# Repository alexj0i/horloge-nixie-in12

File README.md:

# Horloge nixie IN-12

Afficheur 4 chiffres à tubes nixie **IN-12A / IN-12B**, avec deux points en néons **INS-1**.
Un décodeur **SN74141 / K155ID1** par tube (pilotage statique). Chaque tube est monté sur son propre porte-tube, enfiché sur la carte mère.
Deux cartes empilées derrière la carte mère remplacent l'Arduino Uno et le module HT (tout en traversant) : une carte logique (ATmega328P, 74HC595, horloge DS1307) et une carte alimentation (12 V, 5 V, 170 V intégré, boutons).

## Contenu

| Dossier | Contenu | État |
|---|---|---|
| `porte_tube_in12/` | Porte-tube individuel 25,4 × 36 mm, tube sur 12 douilles Ø 1 mm, R d'anode 12 kΩ | v1.0 terminé |
| `porte_tube_in12/fabrication/` | Gerbers + perçages prêts pour JLCPCB | à jour avec v1.0 |
| `carte_mere_in12/` | Carte mère 114,3 × 36 mm : 4 supports de porte-tubes, 4 × SN74141, 2 néons INS-1, connecteurs | schéma v0.3, routage en cours |
| `carte_mere_in12/docs/` | Schéma de la carte mère en PDF | v0.3 |
| `carte_logique_in12/` | Carte logique 114,3 × 36 mm, contre la carte mère : ATmega328P, 2 × 74HC595, DS1307, pilotage des deux points | schéma v0.1, composants placés, à router |
| `carte_alim_in12/` | Carte alimentation 114,3 × 36 mm, à l'arrière : jack 12 V, 5 V (L7805), 170 V (MC34063A + IRF740), coupure HT, boutons, ICSP, FTDI, pile CR1220 | schéma v0.1, composants placés, à router |
| `carte_*_in12/docs/` | Schémas en PDF et vues de placement | v0.1 |
| `firmware/nixie_in12/` | Programme Arduino pour le montage avec un Uno (horloge, affichage d'un nombre, anti-empoisonnement) | fonctionnel, à réécrire pour les nouvelles cartes |
| `docs/` | Photos du tube IN-12 et du néon INS-1 | |

Projets KiCad 10. Les symboles et empreintes sont dans chaque dossier de projet (`*.kicad_sym`, `*.pretty`) : rien à installer.

## Carte mère : connecteurs

| Réf. | Rôle | Broches |
|---|---|---|
| J1–J8 | Supports des porte-tubes (gauche / droite de V1…V4) | gauche : K5 K4 K3 K2 K1 virgule – ; droite : K6 K7 K8 K9 K0 (clé) **+HT** |
| J9 | Commande V1, V2 (2×4, au dos) | 1-4 : V1 A B C D · 5-8 : V2 A B C D |
| J12 | Commande V3, V4 (2×4, au dos) | 1-4 : V3 A B C D · 5-8 : V4 A B C D |
| J10 | Logique (au dos) | 1 : +5 V · 2 : GND |
| J11 | Haute tension (au dos) | 1 : **+HT 170 V** · 2 : clé · 3 : GND |
| J13 | Deux points (au dos) | 1 : DOT1_A · 3 : DOT2_A · 5 : DOT_K (2 et 4 sans broche) |
| DS1, DS2 | Néons INS-1 dans l'espace central entre V2 et V3 | 1 : anode · 2 : cathode |

Empilement (entretoises M2 × 11 entre chaque carte, mêmes 16 trous) :
carte mère → **carte logique** (supports P1 à P5 sur J9, J12, J10, J11, J13) → **carte alimentation** (JB1 2 × 10 sur JA1, JB2 1 × 3 +HT sur JA2).

Liaison JA1/JB1 : 1 +5V · 2 GND · 3 RESET · 4 DTR · 5 MOSI · 6 MISO · 7 SCK · 8 RXD · 9 TXD · 10 HV_EN · 11 BTN_MODE · 12 BTN_PLUS · 13 BTN_MINUS · 14 LDR · 15 +5V · 16 GND · 17 +5V · 18 GND · 19 VBAT · 20 GND.
Liaison JA2/JB2 : 1 +HT · 2 sans broche · 3 GND.

Câblage vers l'Uno attendu par le programme (`BCD_PIN`) :

| Tube | A | B | C | D |
|---|---|---|---|---|
| V1 (J9 1-4) | D13 | D11 | D10 | D12 |
| V2 (J9 5-8) | D9 | D7 | D6 | D8 |
| V3 (J12 1-4) | D5 | D3 | D2 | D4 |
| V4 (J12 5-8) | A3 | A1 | A0 | A2 |

Masse commune entre l'Arduino, la carte mère et le module HT.

## Programme

Moniteur série 9600 bauds, fin de ligne « Nouvelle ligne » :
`T1435` règle l'heure à 14:35 · `N42` affiche 42 · `H` retour à l'horloge · `C` défilement anti-empoisonnement.

## Reste à faire

- Carte mère : relier le +5 V entre V1, V2 et V3, et la masse de C1 ; placer et router DS1, DS2, J13 ; DRC à 0 avant commande.
- Cartes logique et alimentation : router les PCB (composants déjà placés), puis réécrire le firmware (74HC595, DS1307, boutons, coupure HT, deux points).
- Mesurer le diamètre de la queue des douilles (perçage prévu pour 0,5–0,75 mm).
- Vérifier le brochage sur un vrai tube avant de souder (anode = broche 1).
- Option : points de séparation INS-1 dans l'espace central de la carte mère.

## Sécurité

170 V continu sur les porte-tubes et J11. Débrancher l'alimentation et attendre que la sortie HT soit sous 10 V avant de toucher la carte.

## Travailler sur deux PC

Un seul PC à la fois sur un même projet : **Fetch/Pull** avant d'ouvrir KiCad, **Commit + Push** après l'avoir fermé.

## Licence

[CC BY-NC-SA 4.0](LICENSE) : fabrication et modifications libres pour un usage personnel, en citant l'auteur. **Vente et usage commercial interdits** sans accord écrit. Les versions modifiées doivent être publiées sous la même licence.
Quelques empreintes et symboles viennent des bibliothèques KiCad et restent sous CC-BY-SA 4.0 : voir [LICENCES.md](LICENCES.md).

Projet fourni sans garantie. Il utilise une haute tension de 170 V : si vous le reproduisez, c'est à vos risques.

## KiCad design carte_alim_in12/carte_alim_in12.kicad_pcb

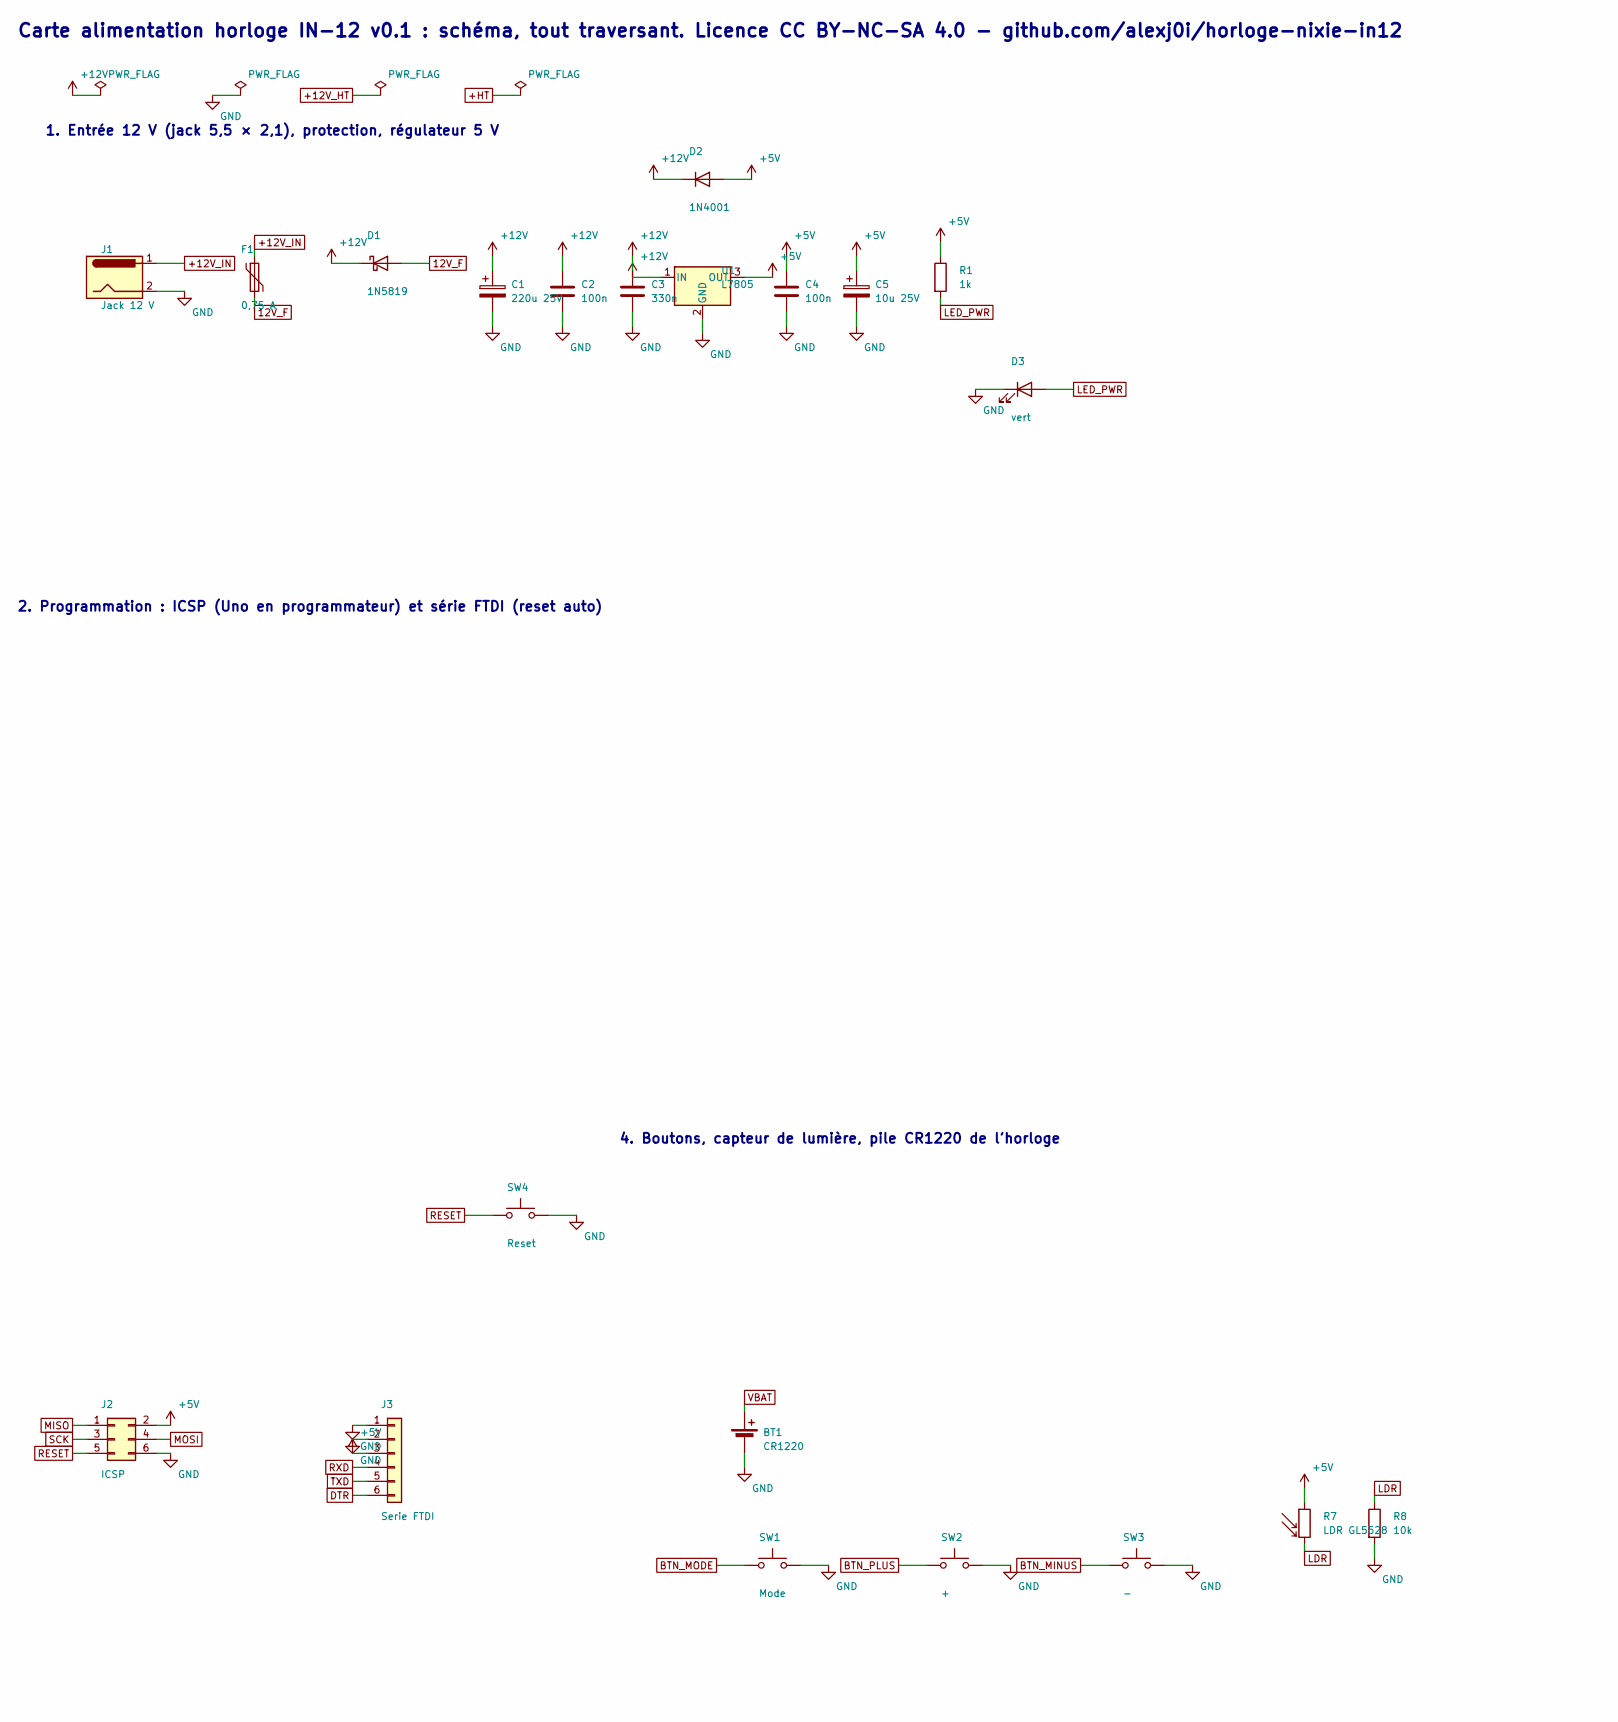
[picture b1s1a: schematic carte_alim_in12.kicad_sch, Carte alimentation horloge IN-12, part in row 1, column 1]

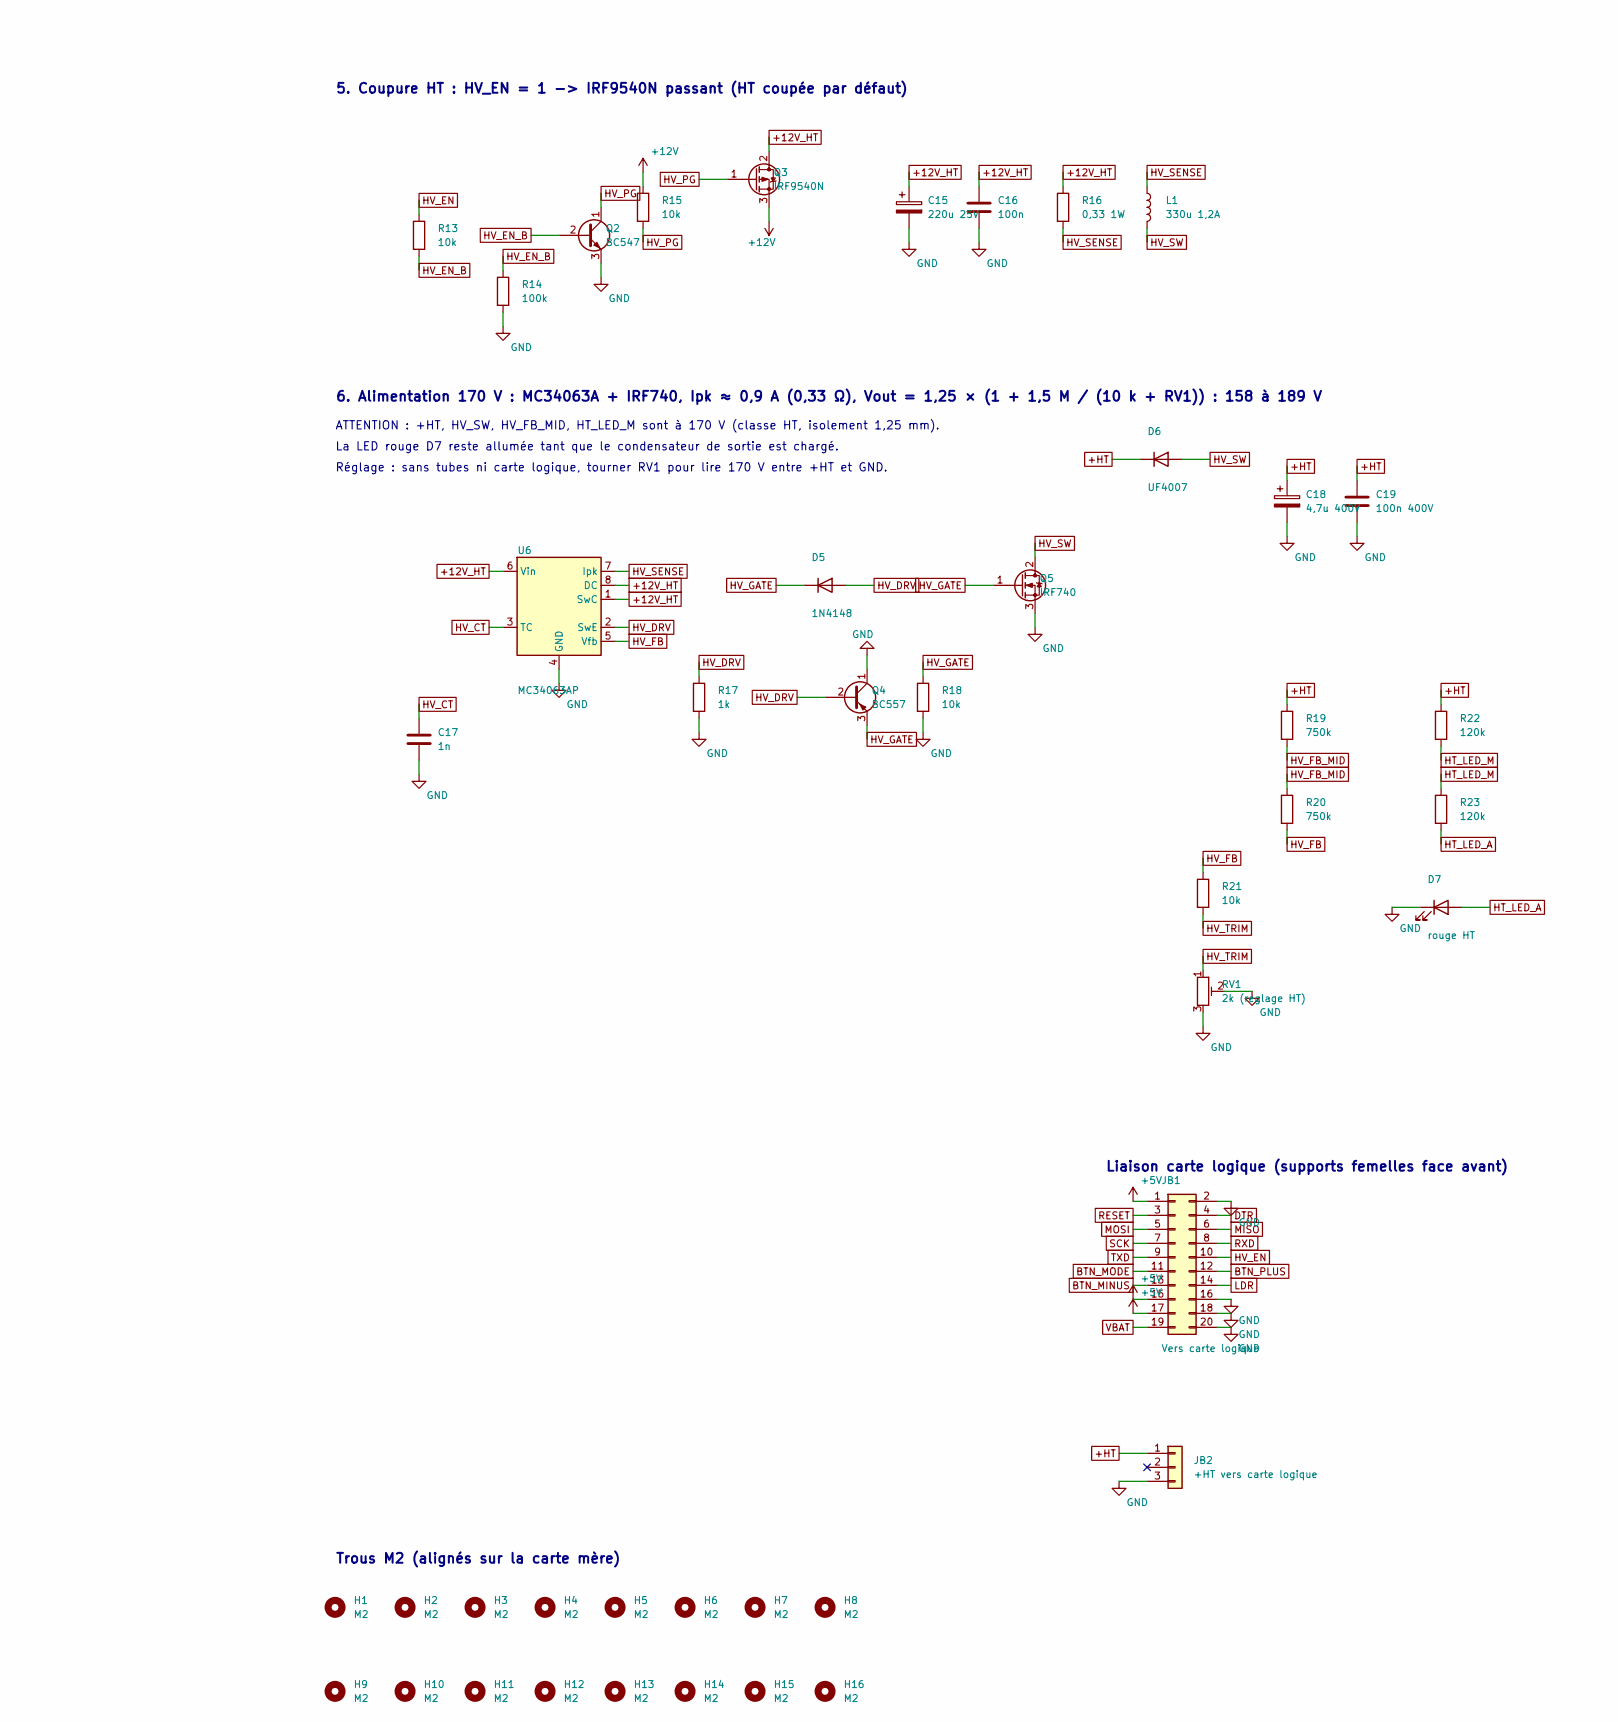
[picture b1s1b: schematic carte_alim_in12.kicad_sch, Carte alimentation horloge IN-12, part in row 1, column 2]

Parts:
BT1: CR1220; BatteryHolder_Keystone_3001_1x12mm
C1, C15: 220u 25V; CP_Radial_D8.0mm_P3.50mm
C2, C4, C16: 100n; C_Disc_D3.0mm_W1.6mm_P2.50mm
C3: 330n; C_Disc_D3.0mm_W1.6mm_P2.50mm
C5: 10u 25V; CP_Radial_D5.0mm_P2.00mm
C17: 1n; C_Disc_D3.0mm_W1.6mm_P2.50mm
C18: 4,7u 400V; CP_Radial_D10.0mm_P5.00mm
C19: 100n 400V; C_Rect_L10.0mm_W4.0mm_P7.50mm_FKS3_FKP3
D1: 1N5819; D_DO-41_SOD81_P3.81mm_Vertical_AnodeUp
D2: 1N4001; D_DO-41_SOD81_P3.81mm_Vertical_AnodeUp
D3: vert; LED_D3.0mm
D5: 1N4148; D_DO-35_SOD27_P7.62mm_Horizontal
D6: UF4007; D_DO-41_SOD81_P10.16mm_Horizontal
D7: rouge HT; LED_D3.0mm
F1: 0,75 A; Fuse_BelFuse_0ZRE0075FF_L11.5mm_W4.8mm
H1, H2, H3, H4, H5, H6, H7, H8, H9, H10, H11, H12, H13, H14, H15, H16: M2; MountingHole_2.2mm_M2
J1: Jack 12 V; BarrelJack_Horizontal
J2: ICSP; PinHeader_2x03_P2.54mm_Vertical
J3: Serie FTDI; PinHeader_1x06_P2.54mm_Vertical
JB1: Vers carte logique; PinSocket_2x10_P2.54mm_Vertical
JB2: +HT vers carte logique; Socket_1x03_Cle2
L1: 330u 1,2A; L_Radial_D12.5mm_P7.00mm_Fastron_09HCP
Q2: BC547; TO-92_Inline
Q3: IRF9540N; TO-220-3_Vertical
Q4: BC557; TO-92_Inline
Q5: IRF740; TO-220-3_Vertical
R1, R17: 1k; R_Axial_DIN0207_L6.3mm_D2.5mm_P2.54mm_Vertical
R7: LDR GL5528; R_LDR_5.1x4.3mm_P3.4mm_Vertical
R8, R13, R15, R18, R21: 10k; R_Axial_DIN0207_L6.3mm_D2.5mm_P2.54mm_Vertical
R14: 100k; R_Axial_DIN0207_L6.3mm_D2.5mm_P2.54mm_Vertical
R16: 0,33 1W; R_Axial_DIN0414_L11.9mm_D4.5mm_P5.08mm_Vertical
R19, R20: 750k; R_Axial_DIN0207_L6.3mm_D2.5mm_P7.62mm_Horizontal
R22, R23: 120k; R_Axial_DIN0207_L6.3mm_D2.5mm_P7.62mm_Horizontal
RV1: 2k (reglage HT); Potentiometer_Bourns_3296W_Vertical
SW1: Mode; SW_PUSH_1P1T_6x3.5mm_H5.0_APEM_MJTP1250
SW2: +; SW_PUSH_1P1T_6x3.5mm_H5.0_APEM_MJTP1250
SW3: -; SW_PUSH_1P1T_6x3.5mm_H5.0_APEM_MJTP1250
SW4: Reset; SW_PUSH_1P1T_6x3.5mm_H5.0_APEM_MJTP1250
U1: L7805; TO-220-3_Vertical
U6: MC34063AP; DIP-8_W7.62mm

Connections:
12V_F: D1.2 (A), F1.2
+5V: C4.1, C5.1, D2.2 (A), J2.2, J3.3, JB1.1, JB1.15, JB1.17, R1.1, R7.1, U1.3 (OUT)
+12V: C1.1, C2.1, C3.1, D1.1 (K), D2.1 (K), Q3.3 (S), R15.1, U1.1 (IN)
+12V_HT: C15.1, C16.1, Q3.2 (D), R16.1, U6.1 (SwC), U6.6 (Vin), U6.8 (DC)
+12V_IN: F1.1, J1.1
+HT: C18.1, C19.1, D6.1 (K), JB2.1, R19.1, R22.1
BTN_MINUS: JB1.13, SW3.1
BTN_MODE: JB1.11, SW1.1
BTN_PLUS: JB1.12, SW2.1
DTR: J3.6, JB1.4
GND: BT1.2 (-), C1.2, C2.2, C3.2, C4.2, C5.2, C15.2, C16.2, C17.2, C18.2, C19.2, D3.1 (K), D7.1 (K), J1.2, J2.6, J3.1, J3.2, JB1.2, JB1.16, JB1.18, JB1.20, JB2.3, Q2.3 (E), Q4.1 (C), Q5.3 (S), R8.2, R14.2, R17.2, R18.2, RV1.2, RV1.3, SW1.2, SW2.2, SW3.2, SW4.2, U1.2 (GND), U6.4 (GND)
HT_LED_A: D7.2 (A), R23.2
HT_LED_M: R22.2, R23.1
HV_CT: C17.1, U6.3 (TC)
HV_DRV: D5.2 (A), Q4.2 (B), R17.1, U6.2 (SwE)
HV_EN: JB1.10, R13.1
HV_EN_B: Q2.2 (B), R13.2, R14.1
HV_FB: R20.2, R21.1, U6.5 (Vfb)
HV_FB_MID: R19.2, R20.1
HV_GATE: D5.1 (K), Q4.3 (E), Q5.1 (G), R18.1
HV_PG: Q2.1 (C), Q3.1 (G), R15.2
HV_SENSE: L1.1, R16.2, U6.7 (Ipk)
HV_SW: D6.2 (A), L1.2, Q5.2 (D)
HV_TRIM: R21.2, RV1.1
LDR: JB1.14, R7.2, R8.1
LED_PWR: D3.2 (A), R1.2
MISO: J2.1, JB1.6
MOSI: J2.4, JB1.5
RESET: J2.5, JB1.3, SW4.1
RXD: J3.4, JB1.8
SCK: J2.3, JB1.7
TXD: J3.5, JB1.9
VBAT: BT1.1 (+), JB1.19

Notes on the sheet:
1. Entrée 12 V (jack 5,5 × 2,1), protection, régulateur 5 V
2. Programmation : ICSP (Uno en programmateur) et série FTDI (reset auto)
4. Boutons, capteur de lumière, pile CR1220 de l'horloge
5. Coupure HT : HV_EN = 1 -> IRF9540N passant (HT coupée par défaut)
6. Alimentation 170 V : MC34063A + IRF740, Ipk ≈ 0,9 A (0,33 Ω), Vout = 1,25 × (1 + 1,5 M / (10 k + RV1)) : 158 à 189 V
Liaison carte logique (supports femelles face avant)
Trous M2 (alignés sur la carte mère)
ATTENTION : +HT, HV_SW, HV_FB_MID, HT_LED_M sont à 170 V (classe HT, isolement 1,25 mm).
La LED rouge D7 reste allumée tant que le condensateur de sortie est chargé.
Réglage : sans tubes ni carte logique, tourner RV1 pour lire 170 V entre +HT et GND.
Carte alimentation horloge IN-12 v0.1 : schéma, tout traversant. Licence CC BY-NC-SA 4.0 - github.com/alexj0i/horloge-nixie-in12

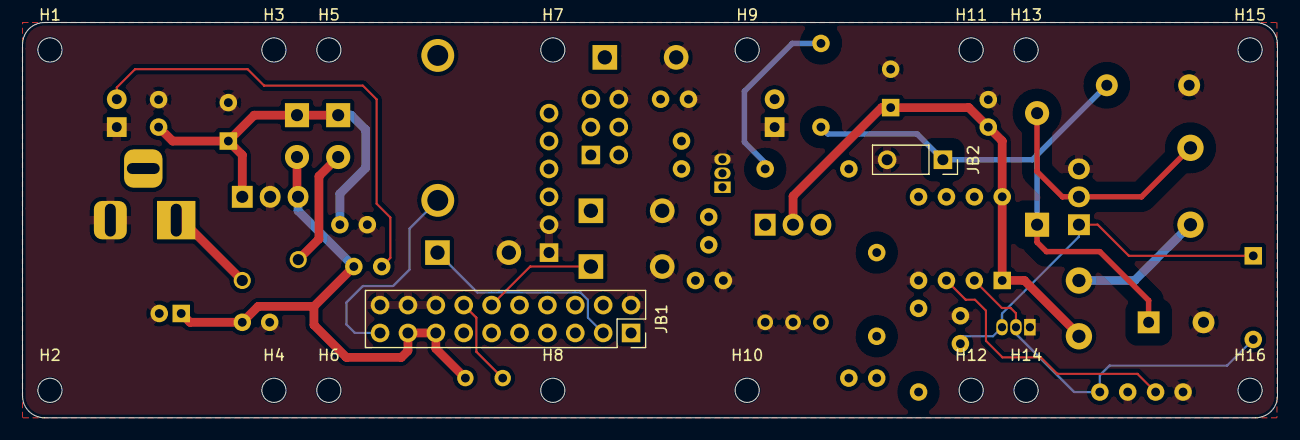
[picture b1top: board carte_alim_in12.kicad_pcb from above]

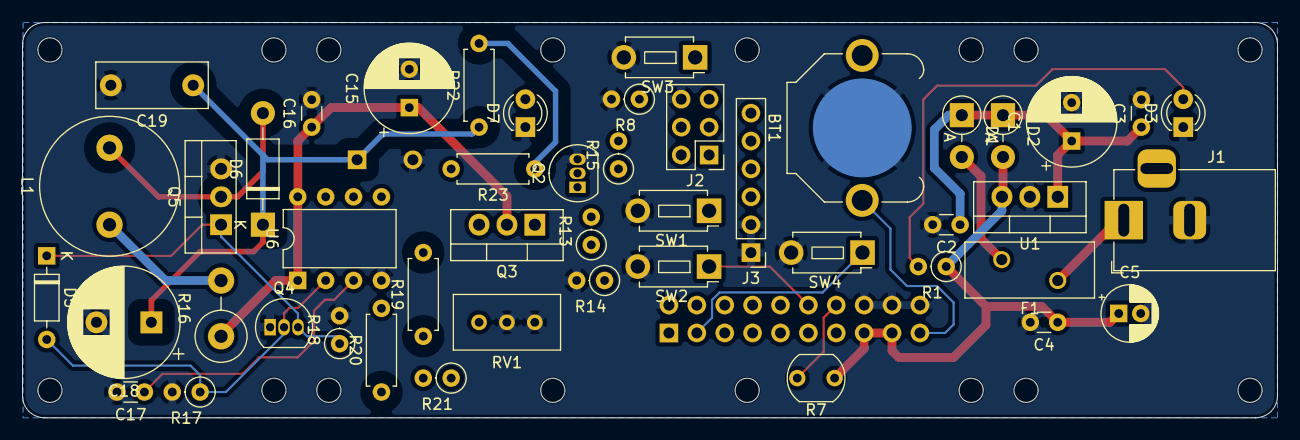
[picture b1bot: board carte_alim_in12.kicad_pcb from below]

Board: 2 copper layers, 114.3 x 36.0 mm, 65 parts (47 on the bottom side), 33 nets.

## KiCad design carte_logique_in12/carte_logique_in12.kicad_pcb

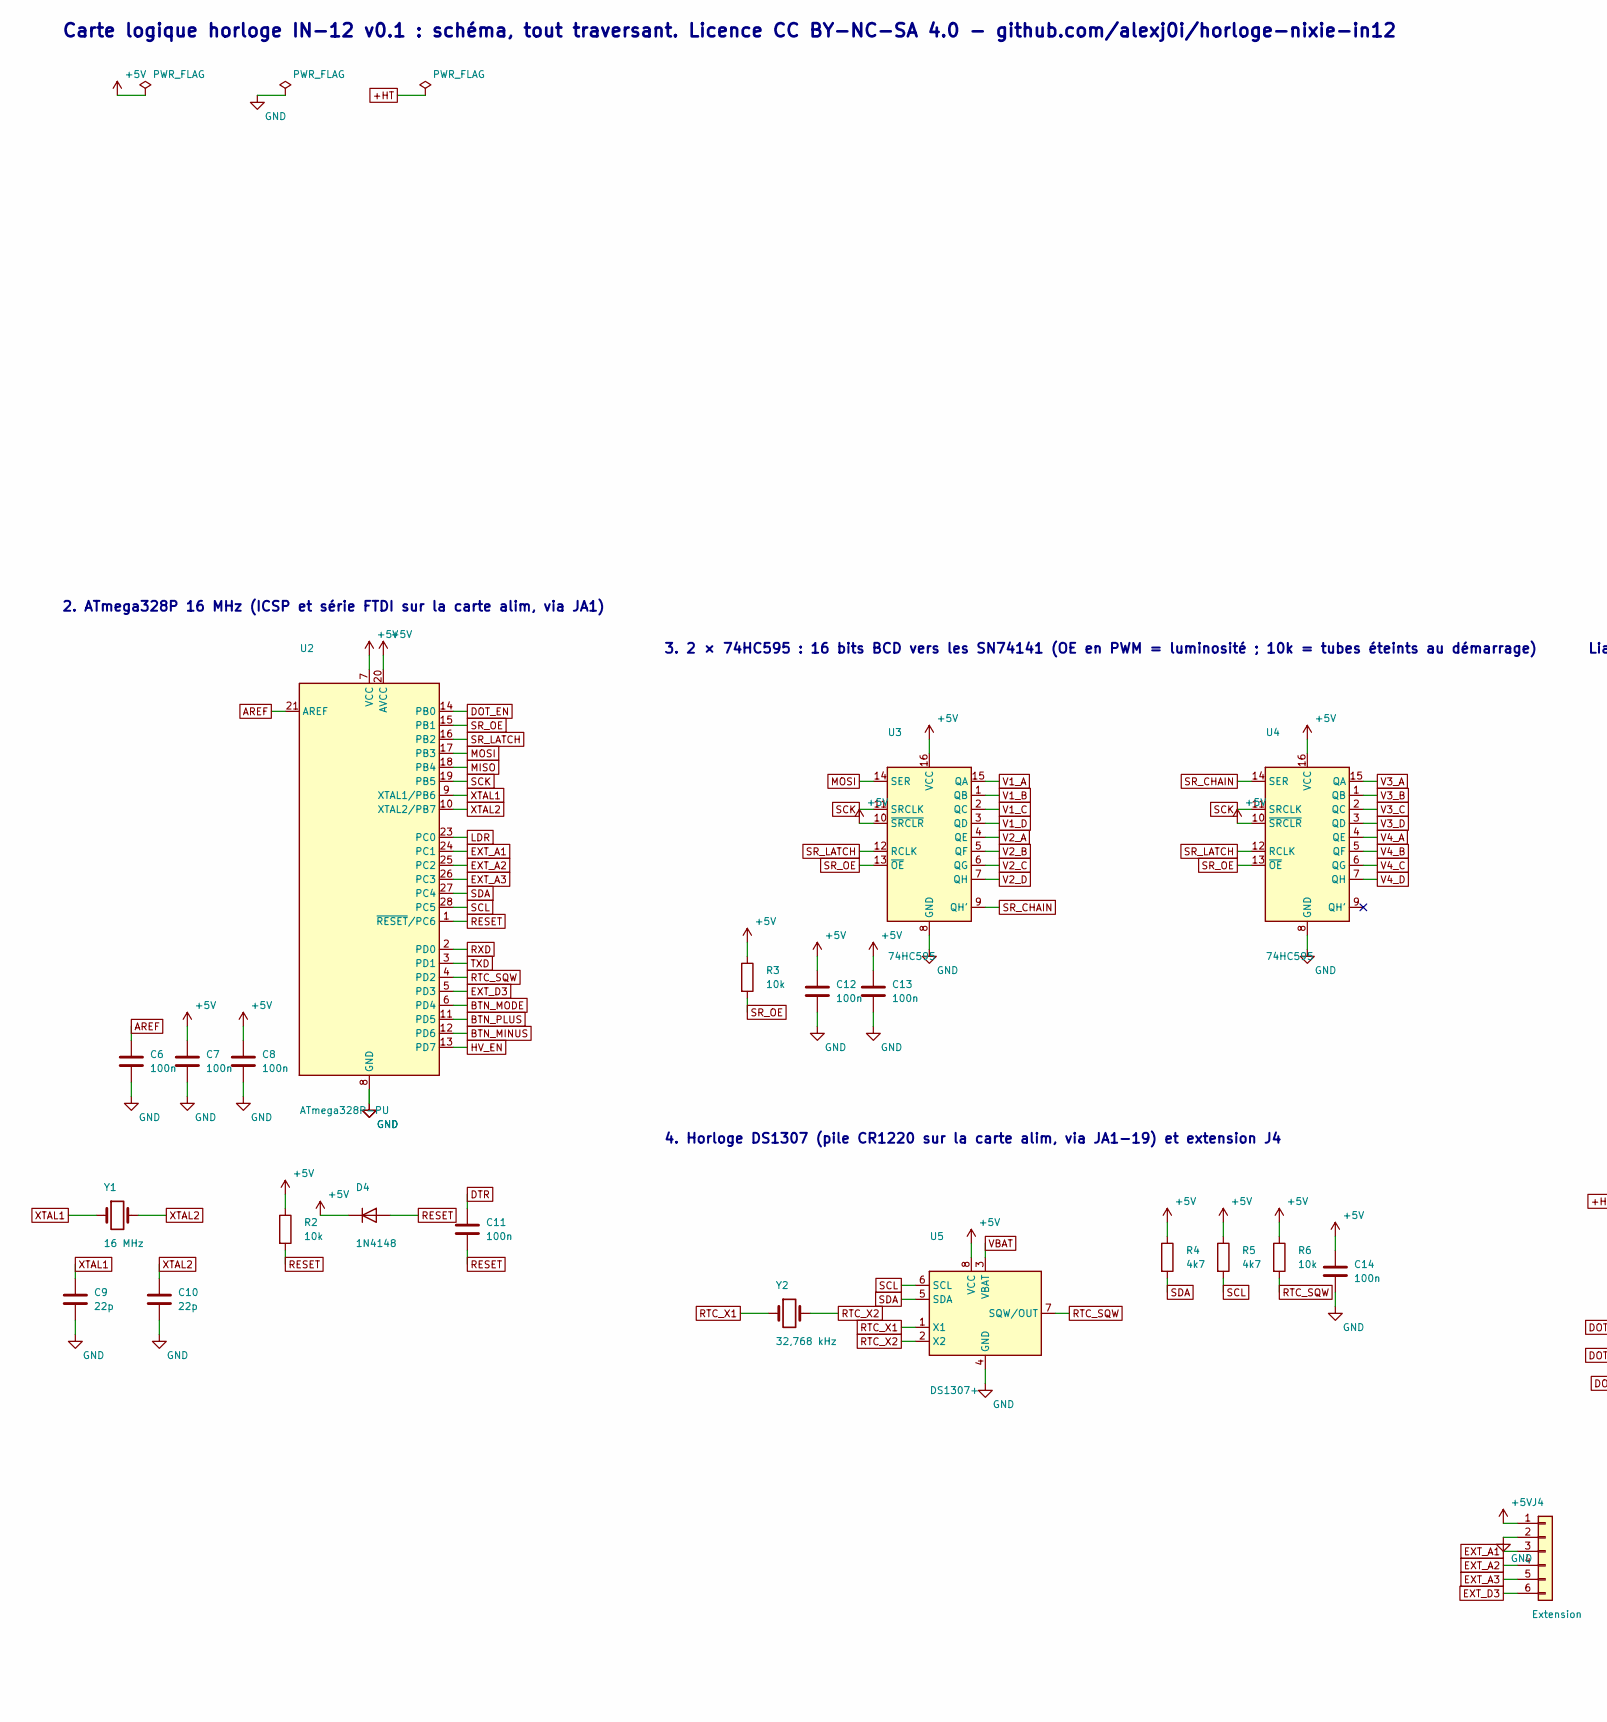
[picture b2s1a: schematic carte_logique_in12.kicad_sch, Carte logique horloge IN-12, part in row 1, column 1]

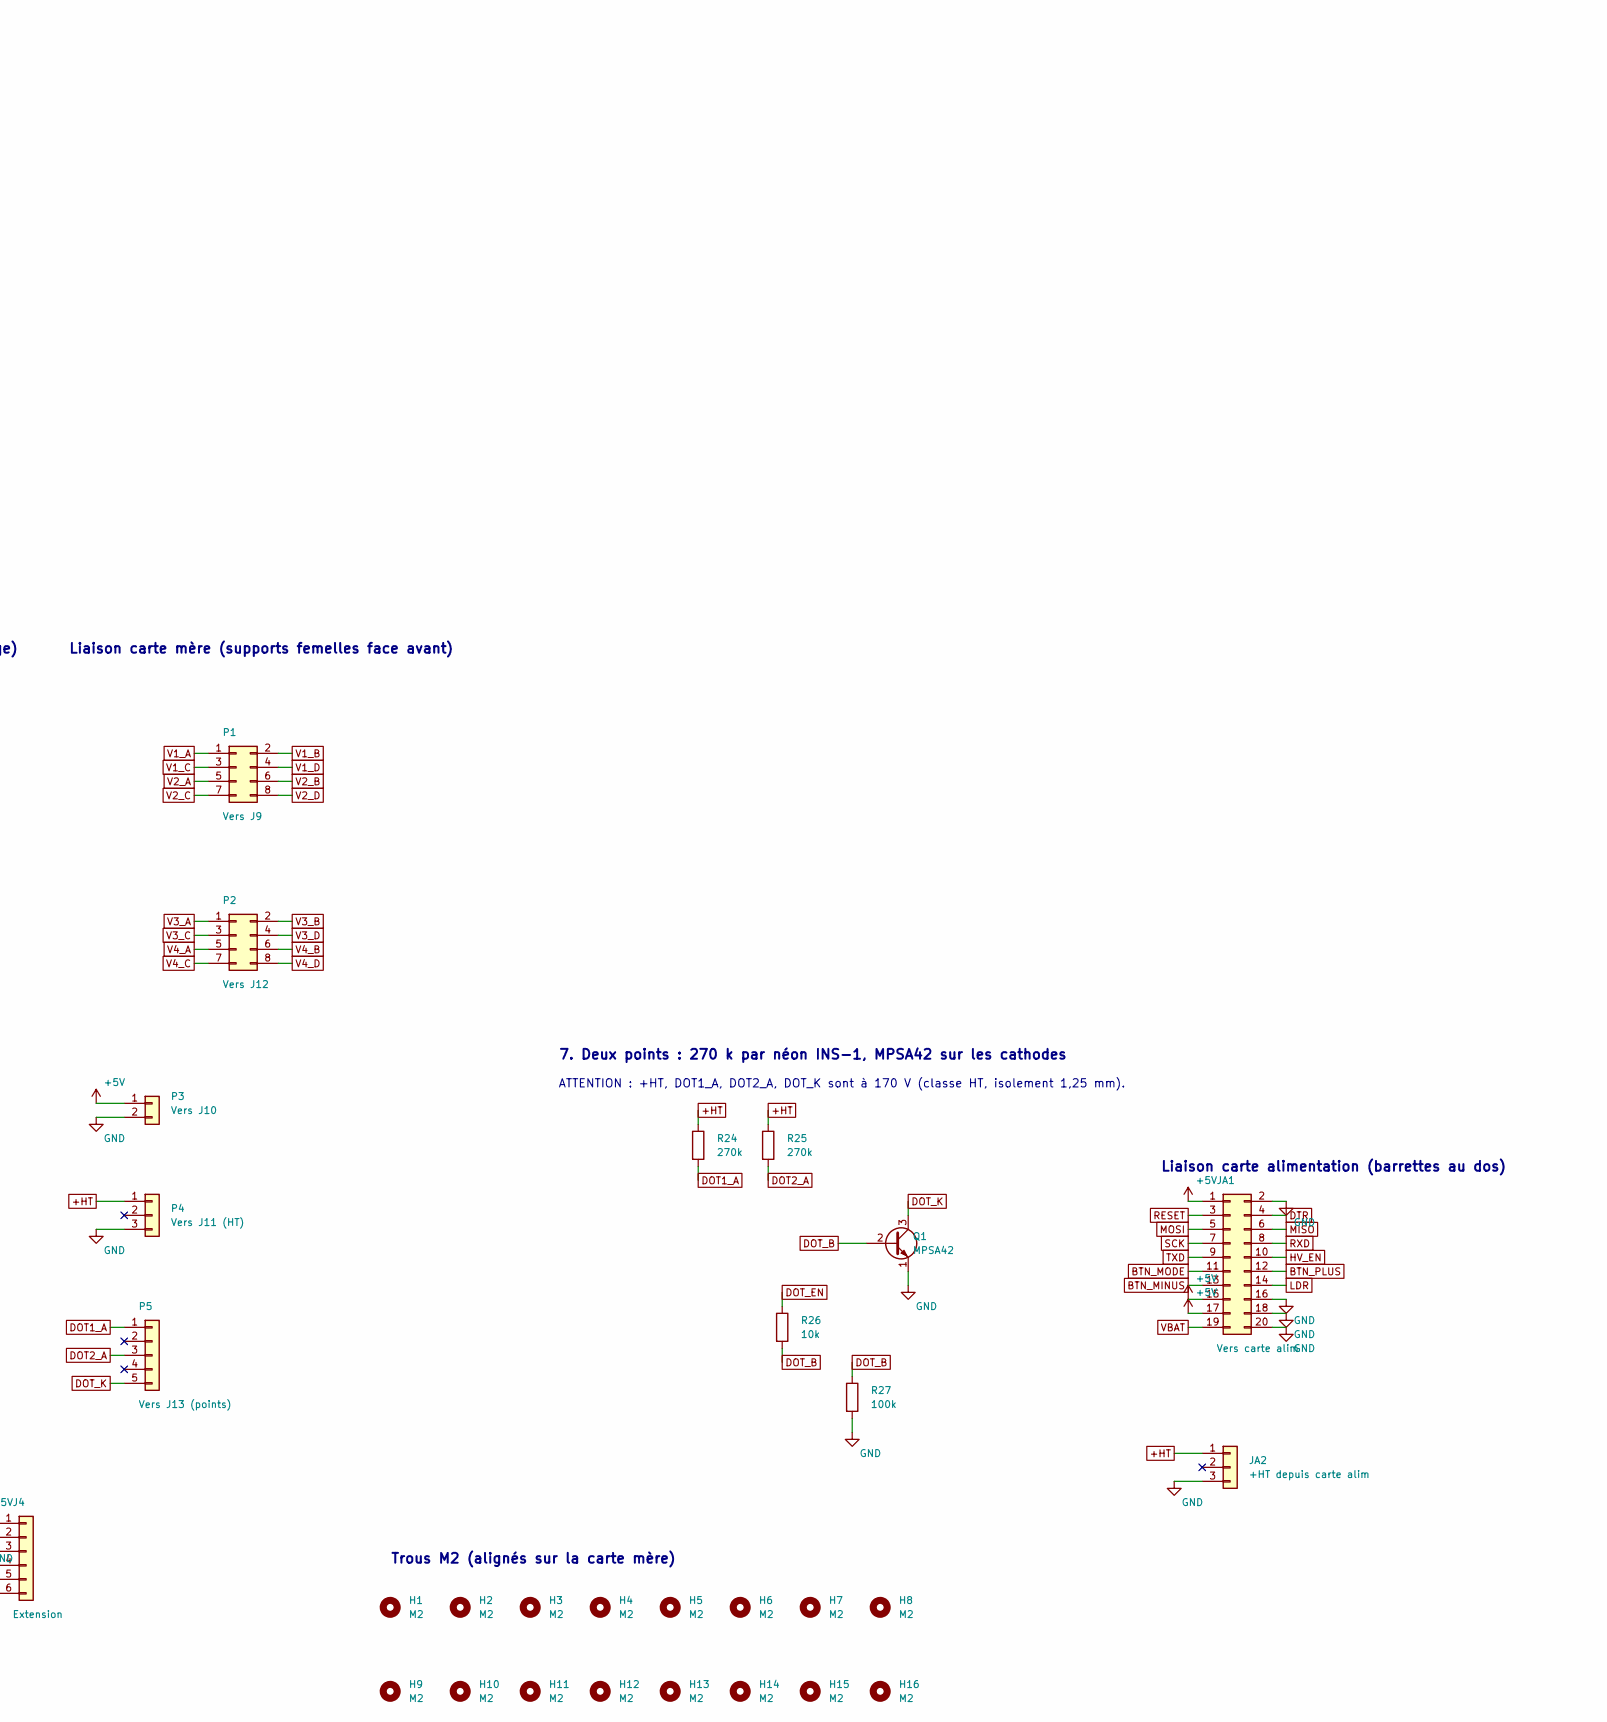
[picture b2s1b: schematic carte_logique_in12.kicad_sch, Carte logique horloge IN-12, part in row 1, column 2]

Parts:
C6, C7, C8, C11, C12, C13, C14: 100n; C_Disc_D3.0mm_W1.6mm_P2.50mm
C9, C10: 22p; C_Disc_D3.0mm_W1.6mm_P2.50mm
D4: 1N4148; D_DO-35_SOD27_P7.62mm_Horizontal
H1, H2, H3, H4, H5, H6, H7, H8, H9, H10, H11, H12, H13, H14, H15, H16: M2; MountingHole_2.2mm_M2
J4: Extension; PinHeader_1x06_P2.54mm_Vertical
JA1: Vers carte alim; PinHeader_2x10_P2.54mm_Vertical
JA2: +HT depuis carte alim; Header_1x03_Cle2
P1: Vers J9; PinSocket_2x04_P2.54mm_Vertical
P2: Vers J12; PinSocket_2x04_P2.54mm_Vertical
P3: Vers J10; PinSocket_1x02_P2.54mm_Vertical
P4: Vers J11 (HT); Socket_1x03_Cle2
P5: Vers J13 (points); Socket_1x05_Cle24
Q1: MPSA42; TO-92_Inline_Wide_HT
R2, R3, R6, R26: 10k; R_Axial_DIN0207_L6.3mm_D2.5mm_P7.62mm_Horizontal
R4, R5: 4k7; R_Axial_DIN0207_L6.3mm_D2.5mm_P7.62mm_Horizontal
R24, R25: 270k; R_Axial_DIN0207_L6.3mm_D2.5mm_P7.62mm_Horizontal
R27: 100k; R_Axial_DIN0207_L6.3mm_D2.5mm_P7.62mm_Horizontal
U2: ATmega328P-PU; DIP-28_W7.62mm
U3, U4: 74HC595; DIP-16_W7.62mm
U5: DS1307+; DIP-8_W7.62mm
Y1: 16 MHz; Crystal_HC49-4H_Vertical
Y2: 32,768 kHz; Crystal_C26-LF_D2.1mm_L6.5mm_Horizontal

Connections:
+5V: C7.1, C8.1, C12.1, C13.1, C14.1, D4.1 (K), J4.1, JA1.1, JA1.15, JA1.17, P3.1, R2.1, R3.1, R4.1, R5.1, R6.1, U2.7 (VCC), U2.20 (AVCC), U3.10 (~SRCLR), U3.16 (VCC), U4.10 (~SRCLR), U4.16 (VCC), U5.8 (VCC)
+HT: JA2.1, P4.1, R24.1, R25.1
AREF: C6.1, U2.21 (AREF)
BTN_MINUS: JA1.13, U2.12 (PD6)
BTN_MODE: JA1.11, U2.6 (PD4)
BTN_PLUS: JA1.12, U2.11 (PD5)
DOT1_A: P5.1, R24.2
DOT2_A: P5.3, R25.2
DOT_B: Q1.2 (B), R26.2, R27.1
DOT_EN: R26.1, U2.14 (PB0)
DOT_K: P5.5, Q1.3 (C)
DTR: C11.1, JA1.4
EXT_A1: J4.3, U2.24 (PC1)
EXT_A2: J4.4, U2.25 (PC2)
EXT_A3: J4.5, U2.26 (PC3)
EXT_D3: J4.6, U2.5 (PD3)
GND: C6.2, C7.2, C8.2, C9.2, C10.2, C12.2, C13.2, C14.2, J4.2, JA1.2, JA1.16, JA1.18, JA1.20, JA2.3, P3.2, P4.3, Q1.1 (E), R27.2, U2.8 (GND), U2.22 (GND), U3.8 (GND), U4.8 (GND), U5.4 (GND)
HV_EN: JA1.10, U2.13 (PD7)
LDR: JA1.14, U2.23 (PC0)
MISO: JA1.6, U2.18 (PB4)
MOSI: JA1.5, U2.17 (PB3), U3.14 (SER)
RESET: C11.2, D4.2 (A), JA1.3, R2.2, U2.1 (~RESET/PC6)
RTC_SQW: R6.2, U2.4 (PD2), U5.7 (SQW/OUT)
RTC_X1: U5.1 (X1), Y2.1
RTC_X2: U5.2 (X2), Y2.2
RXD: JA1.8, U2.2 (PD0)
SCK: JA1.7, U2.19 (PB5), U3.11 (SRCLK), U4.11 (SRCLK)
SCL: R5.2, U2.28 (PC5), U5.6 (SCL)
SDA: R4.2, U2.27 (PC4), U5.5 (SDA)
SR_CHAIN: U3.9 (QH'), U4.14 (SER)
SR_LATCH: U2.16 (PB2), U3.12 (RCLK), U4.12 (RCLK)
SR_OE: R3.2, U2.15 (PB1), U3.13 (~OE), U4.13 (~OE)
TXD: JA1.9, U2.3 (PD1)
V1_A: P1.1, U3.15 (QA)
V1_B: P1.2, U3.1 (QB)
V1_C: P1.3, U3.2 (QC)
V1_D: P1.4, U3.3 (QD)
V2_A: P1.5, U3.4 (QE)
V2_B: P1.6, U3.5 (QF)
V2_C: P1.7, U3.6 (QG)
V2_D: P1.8, U3.7 (QH)
V3_A: P2.1, U4.15 (QA)
V3_B: P2.2, U4.1 (QB)
V3_C: P2.3, U4.2 (QC)
V3_D: P2.4, U4.3 (QD)
V4_A: P2.5, U4.4 (QE)
V4_B: P2.6, U4.5 (QF)
V4_C: P2.7, U4.6 (QG)
V4_D: P2.8, U4.7 (QH)
VBAT: JA1.19, U5.3 (VBAT)
XTAL1: C9.1, U2.9 (XTAL1/PB6), Y1.1
XTAL2: C10.1, U2.10 (XTAL2/PB7), Y1.2

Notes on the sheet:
2. ATmega328P 16 MHz (ICSP et série FTDI sur la carte alim, via JA1)
3. 2 × 74HC595 : 16 bits BCD vers les SN74141 (OE en PWM = luminosité ; 10k = tubes éteints au démarrage)
Liaison carte mère (supports femelles face avant)
4. Horloge DS1307 (pile CR1220 sur la carte alim, via JA1-19) et extension J4
7. Deux points : 270 k par néon INS-1, MPSA42 sur les cathodes
Liaison carte alimentation (barrettes au dos)
Trous M2 (alignés sur la carte mère)
ATTENTION : +HT, DOT1_A, DOT2_A, DOT_K sont à 170 V (classe HT, isolement 1,25 mm).
Carte logique horloge IN-12 v0.1 : schéma, tout traversant. Licence CC BY-NC-SA 4.0 - github.com/alexj0i/horloge-nixie-in12

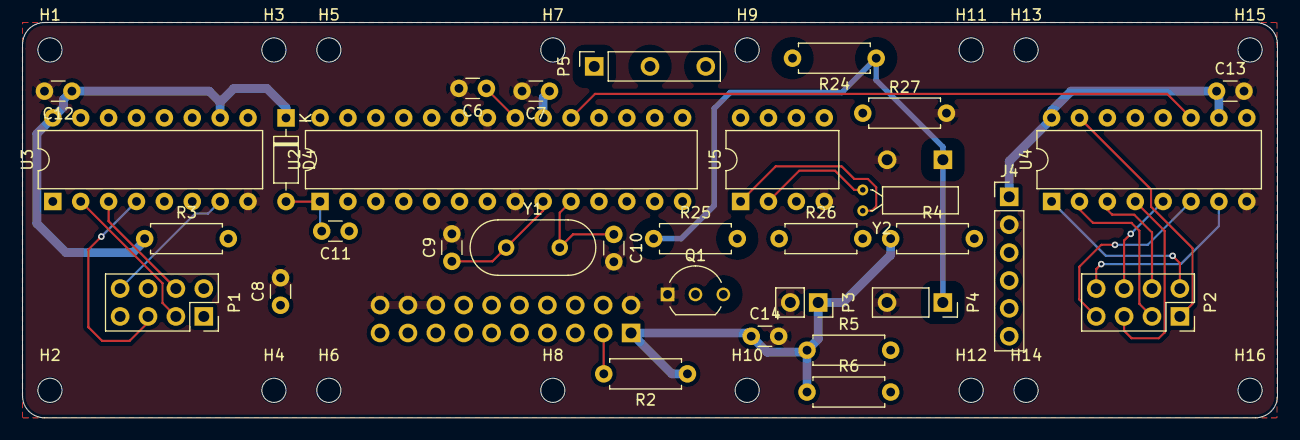
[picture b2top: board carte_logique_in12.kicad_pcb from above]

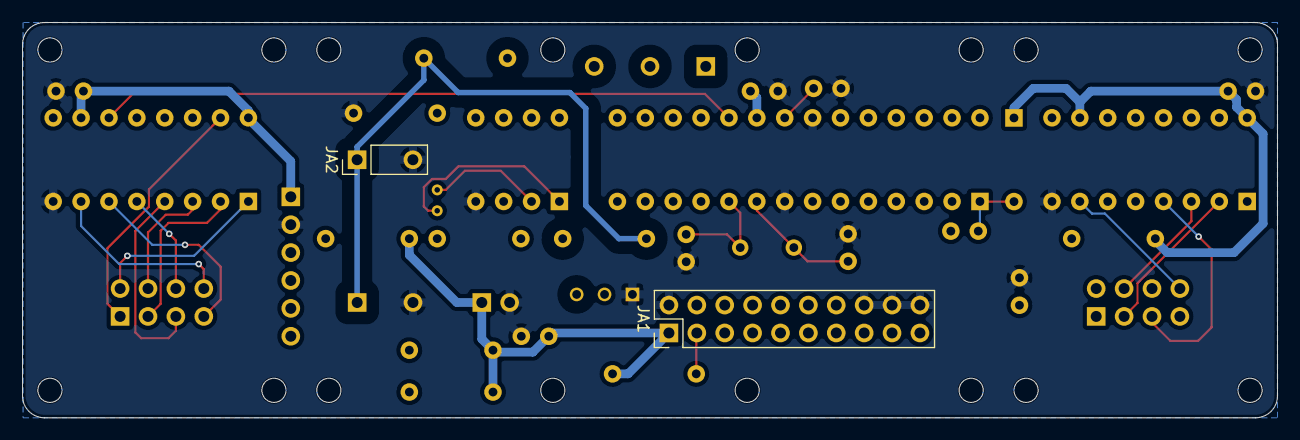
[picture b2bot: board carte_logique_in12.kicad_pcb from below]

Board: 2 copper layers, 114.3 x 36.0 mm, 50 parts (2 on the bottom side), 52 nets.

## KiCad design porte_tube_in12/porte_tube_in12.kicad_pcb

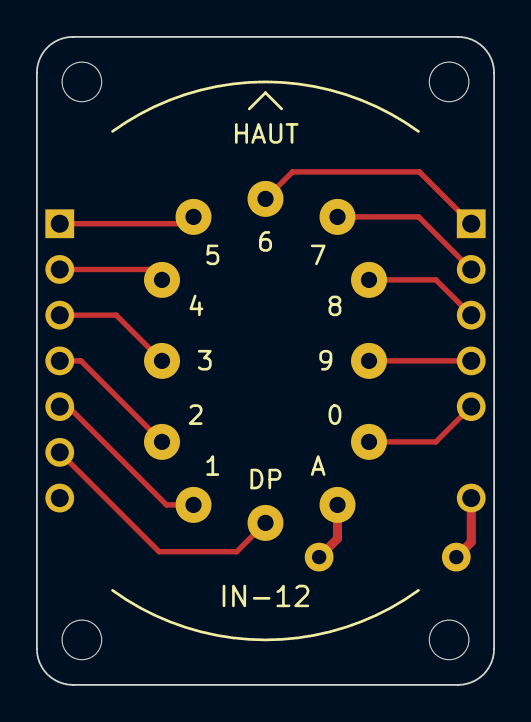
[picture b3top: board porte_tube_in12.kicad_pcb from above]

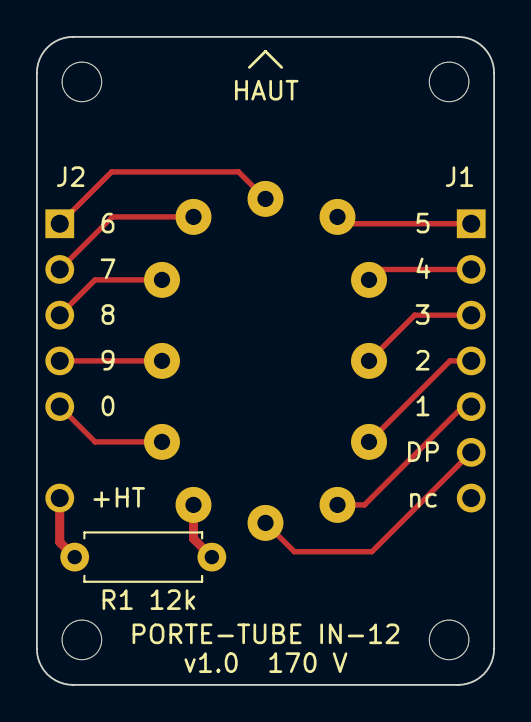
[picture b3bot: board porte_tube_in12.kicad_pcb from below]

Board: 2 copper layers, 25.4 x 36.0 mm, 8 parts (3 on the bottom side), 13 nets.

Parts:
H1, H2, H3, H4: M2; MountingHole_2.2mm_M2
J1: 1x07; Barrette_1x07_P2.54mm_Dos
J2: 1x07 sans 6; Barrette_1x07_Cle6_P2.54mm_Dos
R1: 12k; R_Axial_DIN0207_L6.3mm_D2.5mm_P7.62mm_Horizontal
V1: IN-12B; Nixie_IN-12_Douilles_1mm

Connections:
+HT: J2.7, R1.1
ANODE: R1.2, V1.1
DP: J1.6, V1.12
K0: J2.5, V1.2
K1: J1.5, V1.11
K2: J1.4, V1.10
K3: J1.3, V1.9
K4: J1.2, V1.8
K5: J1.1, V1.7
K6: J2.1, V1.6
K7: J2.2, V1.5
K8: J2.3, V1.4
K9: J2.4, V1.3
